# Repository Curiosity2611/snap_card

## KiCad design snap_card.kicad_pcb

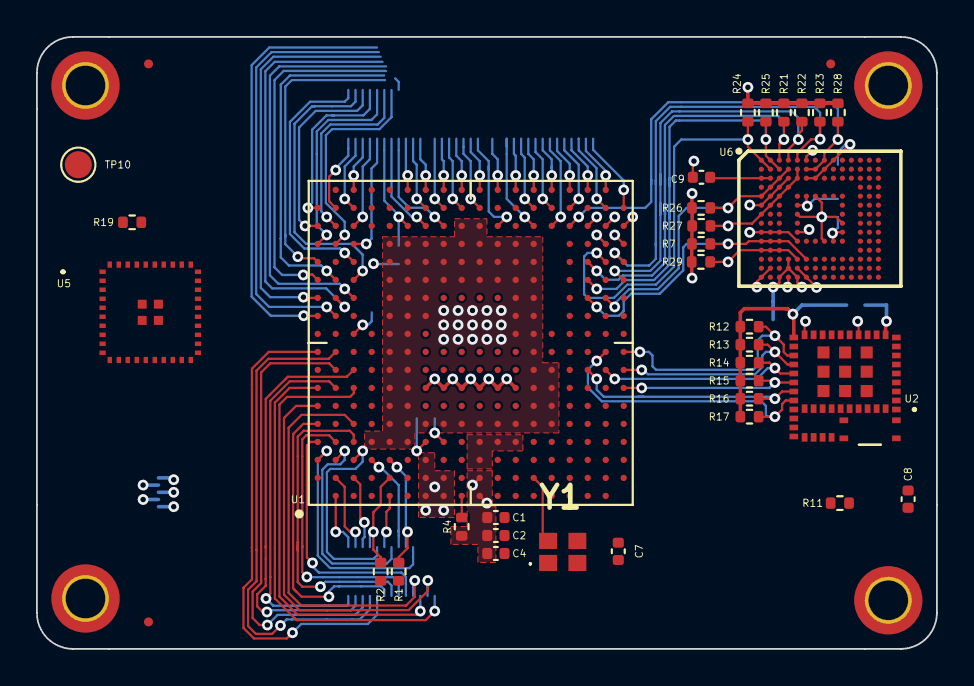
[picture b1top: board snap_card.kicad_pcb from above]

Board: 4 copper layers, 50.0 x 34.0 mm, 58 parts (0 on the bottom side), 146 nets.

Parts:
C1: 1nF; C_0402_1005Metric
C2, C4, C7, C22, C23, C24, C25: 100nF; C_0402_1005Metric
C5, C6, C19, C21: 10uF; C_0402_1005Metric
C8: 0.9pF; C_0402_1005Metric
C9: 2.2uF; C_0402_1005Metric
FID1, FID2, FID3, FID4, FID5, FID6: Fiducial; Fiducial_0.5mm_Mask1mm
H1, H2, H3, H4: MountingHole_Pad; MountingHole_2.2mm_M2_DIN965_Pad_TopBottom
R1, R2, R6, R8: 1K5; R_0402_1005Metric
R3, R4, R21: 10K; R_0402_1005Metric
R5: 1E; R_0402_1005Metric
R7, R22, R23, R24, R25, R26, R27, R28, R29: 50K; R_0402_1005Metric
R11: 50E; R_0402_1005Metric
R12, R13, R14, R15, R16, R17: 82K; R_0402_1005Metric
R19: 0E; R_0402_1005Metric
TP10: TestPoint; TestPoint_Pad_D1.5mm
U1: OSD32MP157F-512M-BAA; OSD32MP15X-BGA-324
U2: WFM200S022XNA3R; WFM200S022XNA3
U3, U4: DF40C-70DP-0.4V(51); DF40C70DP04V51
U5: BGX220S22HNA21R; BGX220S22HNA21
U6: S40FC004C1B2C00000
U7: DF40C-24DP-0.4V(51); DF40C24DP04V51
Y1: ASDK2-32.768KHZ-LR-T3; ASDK232768KHZLRT3

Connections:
5V_VIN: U1.G1, U1.G2, U1.G3, U1.H1, U1.H2, U7.15, U7.17, U7.19, U7.21, U7.23
BLE_RESET: U1.A10, U5.35
BOOT0: U1.J6, U4.13
BOOT1: U1.H6, U4.15
BOOT2: U1.G6, U4.17
DSI_BL_CTRL: U1.A14, U3.56
DSI_CK_N: U1.P16, U3.13
DSI_CK_P: U1.N16, U3.25
DSI_D0_N: U1.P18, U3.15
DSI_D0_P: U1.P17, U3.17
DSI_D1_N: U1.N18, U3.19
DSI_D1_P: U1.N17, U3.21
DSI_LCD_INT: U1.T18, U3.7
DSI_RESET: U1.R17, U3.9
DSI_TE: U1.R18, U3.11
ETH1_CLK125: U1.C15, U3.61
ETH1_GTX_CLK: U1.B9, U4.63
ETH1_MDC: U1.B15, U3.58
ETH1_MDINT: U1.B17, U3.69
ETH1_MDIO: U1.A15, U3.62
ETH1_RXD0: U1.B12, U3.47
ETH1_RXD1: U1.C12, U3.46
ETH1_RXD2: U1.A11, U3.42
ETH1_RXD3: U1.C5, U4.51
ETH1_RX_CLK: U1.C16, U3.63
ETH1_RX_DV: U1.A12, U3.48
ETH1_TXD0: U1.B7, U4.69
ETH1_TXD1: U1.A7, U4.45
ETH1_TXD2: U1.C7, U4.49
ETH1_TXD3: U1.A6, U4.47
ETH1_TX_EN: U1.A9, U4.61
ETH_CLK: U1.C17, U3.67
ETH_NRST: U1.C8, U4.67
GND: C1.2, C2.2, C4.2, C5.2, C6.2, C7.2, C8.1, C9.2, C19.1, C21.2, C22.2, C23.2, C24.2, C25.2, H1.1, H2.1, H3.1, H4.1, R4.2, R11.2, U1.D4, U1.E4, U1.E5, U1.E6, U1.E7, U1.E8, U1.E9, U1.E10, U1.E11, U1.E12, U1.E13, U1.E14, U1.E15, U1.F4, U1.F5, U1.F6, U1.F7, U1.F8, U1.F9, U1.F10, U1.F11, U1.F12, U1.F13, U1.F14, U1.F15, U1.G5, U1.G11, U1.G12, U1.G13, U1.G14, U1.G15, U1.H5, U1.H13, U1.H14, U1.H15, U1.J5, U1.J13, U1.J14, U1.J15, U1.J16, U1.K1, U1.K2, U1.K5, U1.K13, U1.K14, U1.K15, U1.K16, U1.L5, U1.L13, U1.L14, U1.L15, U1.M5, U1.M10, U1.M11, U1.M12, U1.M13, U1.M14, U1.M15, U1.N5, U1.N6, U1.N7, U1.N8, U1.N9, U1.N10, U1.N11, U1.N12, U1.N13, U1.N14, U1.N15, U1.P5, U1.P6, U1.P7, U1.P8, U2.1, U2.4, U2.5, U2.6, U2.7, U2.8, U2.11, U2.18, U2.21, U2.33, U2.35, U2.36, U2.39, U2.41, U2.42, U2.43, U2.44, U2.45, U2.46, U2.48, U2.49, U2.50, U2.51, U2.52, U2.53, U2.54, U2.55, U2.56, U2.57, U2.58, U5.4, U5.5, U5.36, U5.40, U5.41, U5.42, U5.43, U5.44, U6.A6, U6.C4, U6.D3, U6.E2, U6.E7, U6.F1, U6.G5, U6.H10, U6.J5, U6.K8, U6.N2, U6.N5, U6.P1, U6.P4, U6.P6, U7.2, U7.4, U7.6, U7.8, U7.10, U7.12, U7.14, U7.16, Y1.1
GPIO_ANA_1: U1.L1, U4.30
GPIO_ANA_2: U1.L2, U4.32
GPIO_USART1_CTS: U1.E1, U4.60
GPIO_USART1_RTS: U1.L18, U3.29
GPIO_USART1_RX: U1.M18, U3.23
GPIO_USART1_TX: U1.C14, U3.70
HDMI_CEC: U1.H18, U3.43
HDMI_INT: U1.B8, U4.65
HDMI_NRST: U1.L16, U3.33
I2C1_SCL: R8.1, U1.F16, U3.59
I2C1_SDA: R6.1, U1.C10, U3.40
I2C4_SCL: R2.1, U1.E2, U4.64
I2C4_SDA: R1.1, U1.E3, U4.54
I2S2_CK: U1.T11, U3.28
I2S2_SDO: U1.R3, U4.28
I2S2_WS: U1.U13, U3.18
JTCK_SWCLK: U1.R15, U3.12
JTDI: U1.R13, U3.14
JTDO_TRACESWO: U1.R12, U3.20
JTMS_SWDIO: U1.R14, U3.10
LCD_B0: U1.B1, U4.70
LCD_B1: U1.A4, U4.53
LCD_B2: U1.C18, U3.65
LCD_B3: U1.V6, U4.37
LCD_B4: U1.U5, U4.1
LCD_B5: U1.A5, U4.59
LCD_B6: U1.P3, U3.16
LCD_B7: U1.B2, U4.68
LCD_CLK: U1.H17, U3.45
LCD_DE: U1.H16, U3.55
LCD_G0: U1.B11, U3.44
LCD_G1: U1.T9, U3.36
LCD_G2: U1.U1, U4.2
LCD_G3: U1.T1, U4.6
LCD_G4: U1.T2, U4.8
LCD_G5: U1.T3, U4.22
LCD_G6: U1.R1, U4.10
LCD_G7: U1.R2, U4.12
LCD_HSYNC: U1.B4, U4.55
LCD_R0: U1.B13, U3.52
LCD_R1: U1.C13, U3.68
LCD_R2: U1.T4, U4.9
LCD_R3: U1.V3, U4.11
LCD_R4: U1.U3, U4.20
LCD_R5: U1.A17, U3.64
LCD_R6: U1.U2, U4.4
LCD_R7: U1.U4, U4.7
LCD_VSYNC: U1.C2, U4.66
NJRST: U1.R11, U3.22
NRST: R3.2, U1.M3, U2.12, U4.24, U6.J1, U6.J2, U6.J3, U6.K5
unnamed: C8.2, U2.47
unnamed: C9.1, U6.C1, U6.C2
unnamed: C19.2, R5.1, U2.10
unnamed: R4.1, U1.J1
unnamed: R11.1, U2.9
unnamed: R19.1, U5.2
unnamed: R19.2, U5.3
unnamed: TP10.1, U5.25
unnamed: U1.N2, Y1.4
unnamed: U2.2, U2.3
PMIC_LDO1: U1.J4, U7.5
PMIC_LDO2_2V8: C5.1, U1.G4, U7.3
PMIC_LDO6_1V2: C6.1, U1.H4, U7.1
PMIC_VOUT4_3V3: R5.2, R12.1, R13.1, R14.1, R15.1, R16.1, R17.1, U1.H3, U1.J3, U2.20, U2.28, U5.22, U5.23, U7.7, U7.9, U7.11, U7.13
PONKEY: U1.D3, U4.56
SDMMC1_CK: U1.V17, U3.1
SDMMC1_CMD: U1.U18, U3.3
SDMMC1_D0: U1.T16, U3.2
SDMMC1_D1: U1.U16, U4.23
SDMMC1_D2: U1.V16, U4.14
SDMMC1_D3: U1.U17, U3.5
SDMMC2_CK: R7.2, U1.T12, U6.K1, U6.K2, U6.K3, U6.M6
SDMMC2_CMD: R29.2, U1.U15, U6.L1, U6.L2, U6.L3, U6.M5
SDMMC2_D0: R21.2, U1.T14, U6.A3
SDMMC2_D1: R22.2, U1.V13, U6.A4
SDMMC2_D2: R23.2, U1.V14, U6.A5
SDMMC2_D3: R24.2, U1.U14, U6.A1, U6.B2
SDMMC2_D4: R25.2, U1.T13, U6.A2, U6.B3
SDMMC2_D5: R26.2, U1.U12, U6.B4, U6.C3, U6.D2, U6.E1
SDMMC2_D6: R27.2, U1.V15, U6.B5, U6.C5, U6.D4, U6.E3, U6.F2, U6.G1
SDMMC2_D7: R28.2, U1.R16, U6.A8, U6.B6, U6.B7
SDMMC3_CK: R12.2, U1.V9, U2.22
SDMMC3_CMD: R13.2, U1.V8, U2.23
SDMMC3_D0: R14.2, U1.U8, U2.24
SDMMC3_D1: R15.2, U1.V7, U2.25
SDMMC3_D2: R16.2, U1.T8, U2.26
SDMMC3_D3: R17.2, U1.U9, U2.27
SPI5_MISO: U1.G17, U3.51
SPI5_MOSI: U1.G18, U3.49
SPI5_NSS: U1.F18, U3.53
SPI5_SCK: U1.G16, U3.57
STLINK_UART4_RX: U1.V11, U3.34
STLINK_UART4_TX: U1.U11, U3.24
STUSB1600_IRQOUTn: U1.C4, U4.57
USART3_CTS: U1.E18, U5.16
USART3_RTS: U1.D16, U5.17
USART3_RX: U1.B14, U5.11
USART3_TX: U1.A13, U5.15
USB_DM1: U1.K18, U3.35
USB_DM2: U1.J17, U3.41
USB_DP1: U1.K17, U3.37
USB_DP2: U1.J18, U3.39
USB_PWR_CC1: U1.B16, U3.60
USB_PWR_CC2: U1.A16, U3.66
U_BUTTON_1: U1.A3, U4.52
U_BUTTON_2: U1.B3, U4.58
U_LED_1: U1.C3, U4.62
U_LED_2: U1.B10, U3.38
VDD: C7.1, C21.1, C22.1, C23.1, C24.1, C25.1, R1.2, R2.2, R3.1, R6.2, R7.1, R8.2, R21.1, R22.1, R23.1, R24.1, R25.1, R26.1, R27.1, R28.1, R29.1, U1.G7, U1.H7, U1.J7, U1.K3, U1.K4, U1.K7, U1.L4, U1.L6, U1.L7, U1.M4, U1.M6, U1.M7, U6.A9, U6.B8, U6.C6, U6.C7, U6.E6, U6.F5, U6.J10, U6.K9, U6.M4, U6.N4, U6.P3, U6.P5, U7.18, U7.20, U7.22, U7.24, Y1.3
VDDA: C1.1, C2.1, C4.1, U1.M1, U1.M2
WIFI_IRQ: U1.U6, U2.19
WIFI_WKUP: U1.V5, U2.13

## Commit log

2021-05-15 added components list
